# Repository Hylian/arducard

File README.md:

arducard
========

An open-source Arduino derivative e-paper dev device.

Features
-----

* ATmega32U4 (Same as the Arduino Leonardo)
* USB transceiver
* DS1343 Real-Time Clock
* 128KB FRAM
* LiR2016 Coin-cell Li-Ion battery
* Battery charging over USB
* 2.7" e-Paper display
* 5 edge-mounted interrupt-triggered tactile buttons

Dimensions
----------

80 mm x 45 mm x 5 mm

Applications
------------

* Google Auth Time-OTP 
* Store barcodes for rewards cards, etc.
* Store QR codes
* USB text terminal for Raspberry Pi
* ...

Interested?
-----------

Tweet me at [@inwardshed](https://twitter.com/inwardshed) or e-mail at [edshin95@gmail.com](mailto:edshin95@gmail.com) if you're interested in assembling a PCB/contributing.

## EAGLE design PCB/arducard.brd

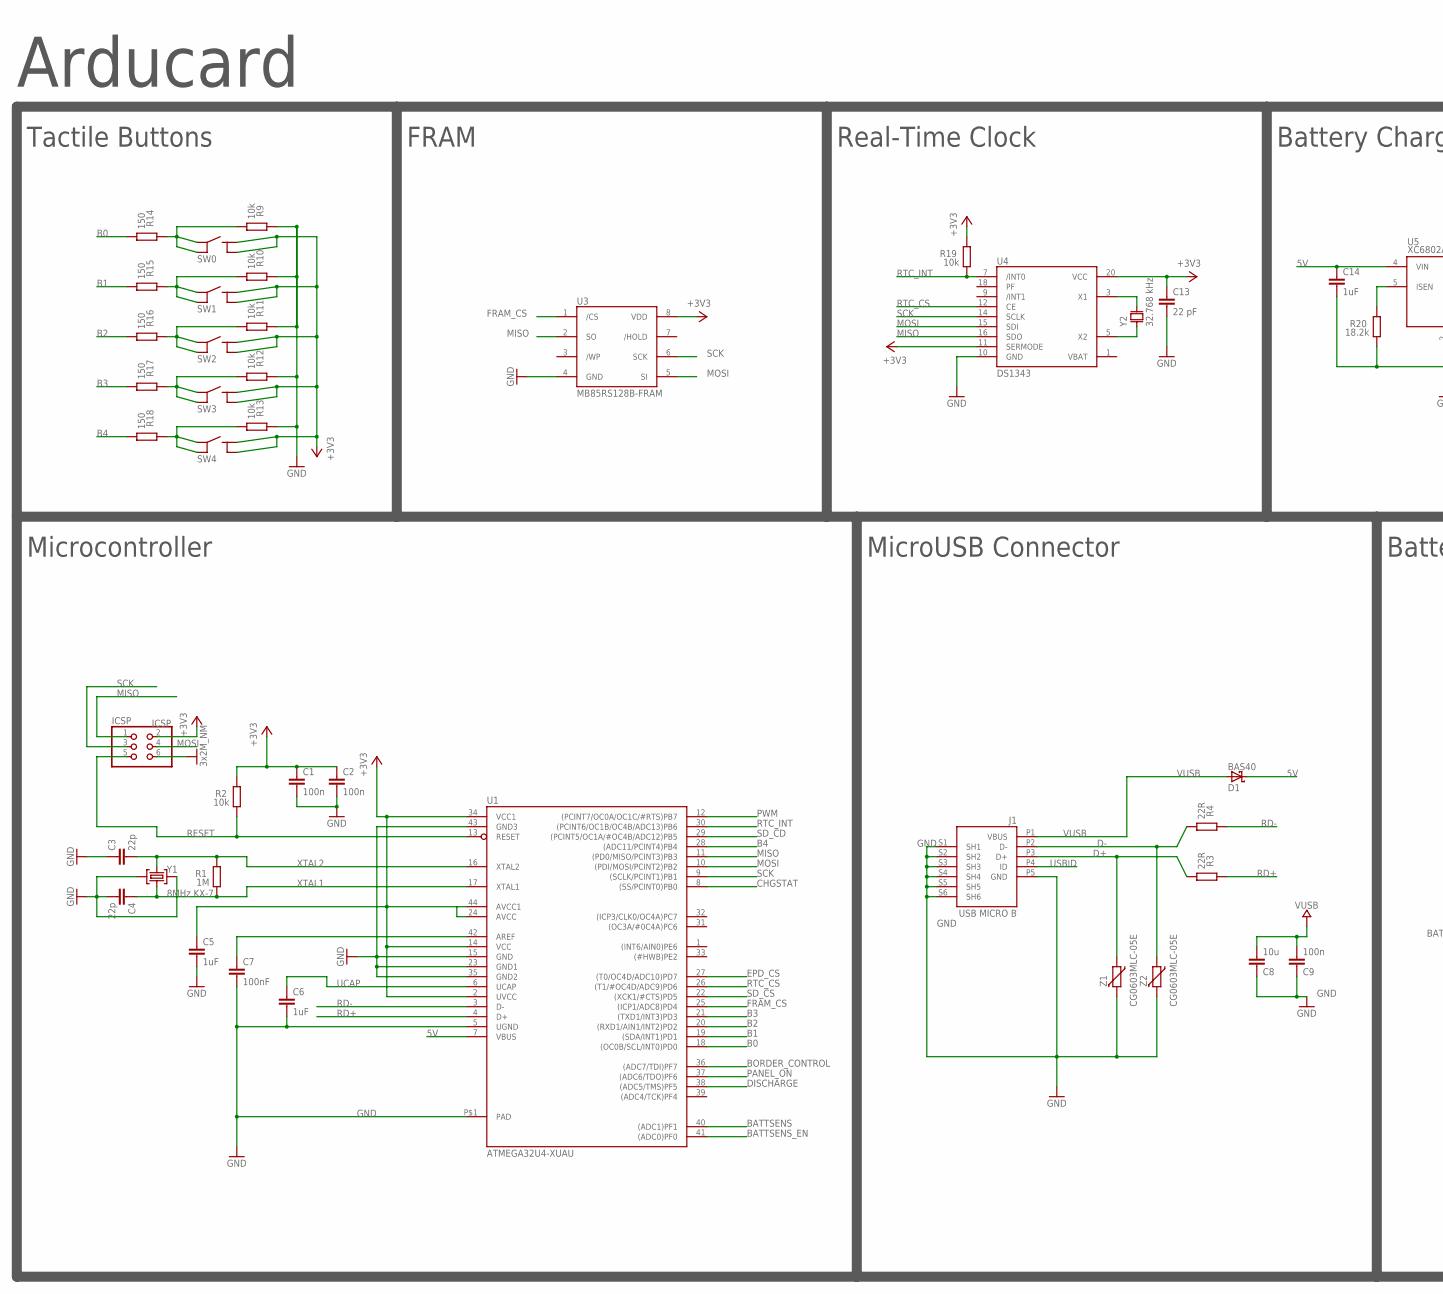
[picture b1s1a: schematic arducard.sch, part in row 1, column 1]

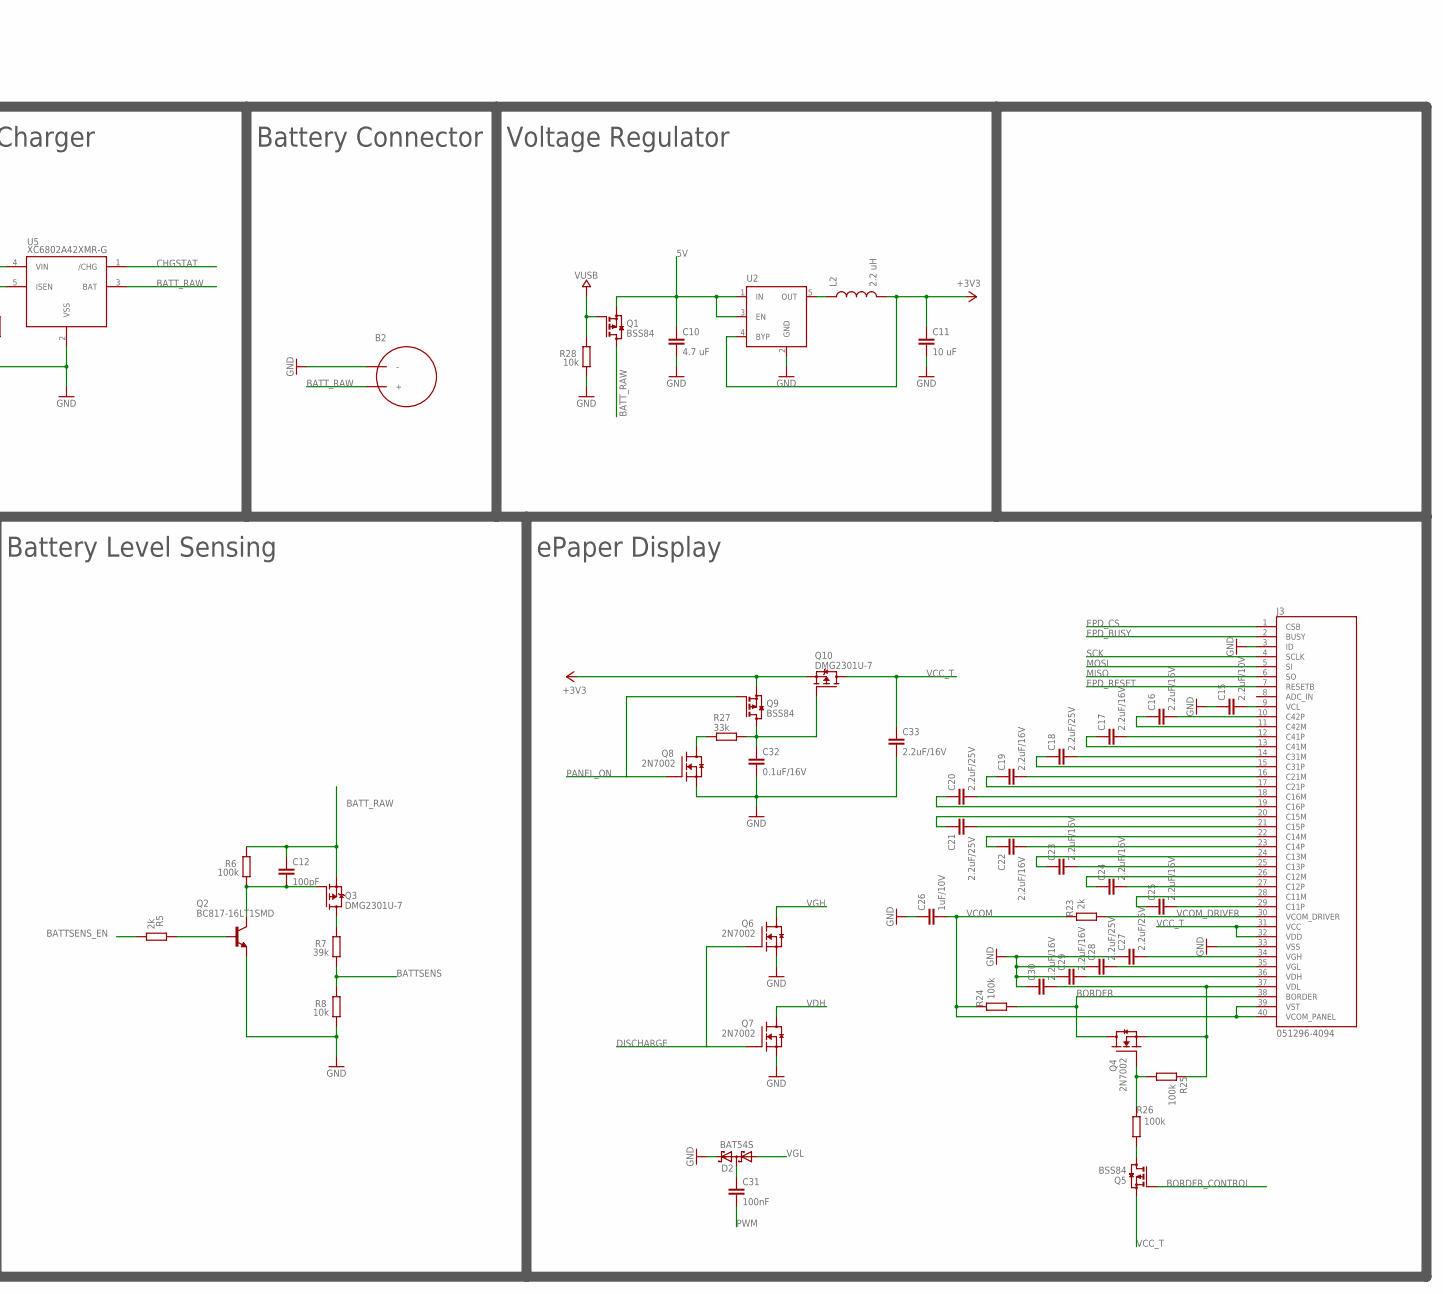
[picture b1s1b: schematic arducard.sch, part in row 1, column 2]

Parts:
B2: LIR2016; BK-5067
C1, C2, C9: 100n; C0603-ROUND
C3, C4: 22p; C0603-ROUND
C5, C6, C14: 1uF; C0603-ROUND
C7, C31: 100nF; C0603-ROUND
C8: 10u; C0603-ROUND
C10: 4.7 uF; C0603-ROUND
C11: 10 uF; C0603-ROUND
C12: 100pF; C0603-ROUND
C13: 22 pF; C0603-ROUND
C15: 2.2uF/10V; C0603-ROUND
C16, C17, C19, C22, C23, C24, C25, C29, C30, C33: 2.2uF/16V; C0603-ROUND
C18, C20, C21, C27, C28: 2.2uF/25V; C0603-ROUND
C26: 1uF/10V; C0603-ROUND
C32: 0.1uF/16V; C0603-ROUND
D1: BAS40; SOT23
D2: BAT54S; SOT23
ICSP: ICSP; 2X03
J1: USB MICRO B; CON2_USB_MICRO_B_AT
J3: 051296-4094
L2: 2.2 uH; 0603
Q1, Q5, Q9: BSS84; SOT23
Q2: BC817-16LT1SMD; SOT23-BEC
Q3, Q10: DMG2301U-7; SOT23
Q4, Q6, Q7, Q8: 2N7002; SOT-23
R1: 1M; R0603-ROUND
R2, R8, R9, R10, R11, R12, R13, R19, R28: 10k; R0603-ROUND
R3, R4: 22R; R0603-ROUND
R5, R23: 2k; R0603-ROUND
R6, R24, R25, R26: 100k; R0603-ROUND
R7: 39k; R0603-ROUND
R14, R15, R16, R17, R18: 150; R0603-ROUND
R20: 18.2k; R0603-ROUND
R27: 33k; R0603-ROUND
SW0, SW1, SW2, SW3, SW4: EVQ-PUA; SMD-TACT-SWITCH
U1: ATMEGA32U4-XUAU; TQFP44-PAD
U2: MIC5219XX; SOT23-5
U3: MB85RS128B-FRAM; SO-08
U4: DS1343; TSSOP20
U5: XC6802A42XMR-G; SOT23-5L
Y1: 8MHz KX-7; CRYSTAL-3.2-2.5
Y2: 32.768 kHz; SSP-T7-F
Z1, Z2: CG0603MLC-05E; CT/CN0603

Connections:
5V: C10.1, C14.1, D1.3 (C), Q1.2 (S), U1.7 (VBUS), U2.1 (IN), U2.3 (EN), U5.4 (VIN)
+3V3: C1.1, C2.1, C5.1, C11.1, C13.1, ICSP.2, L2.2, Q9.2 (S), Q10.2 (S), R2.2, R19.2, SW0.2, SW0.4, SW1.2, SW1.4, SW2.2, SW2.4, SW3.2, SW3.4, SW4.2, SW4.4, U1.2 (UVCC), U1.14 (VCC), U1.24 (AVCC), U1.34 (VCC1), U1.44 (AVCC1), U2.4 (BYP), U3.8 (VDD), U4.11 (SERMODE), U4.20 (VCC)
B0: R14.1, U1.18 ((OC0B/SCL/INT0)PD0)
B1: R15.1, U1.19 ((SDA/INT1)PD1)
B2: R16.1, U1.20 ((RXD1/AIN1/INT2)PD2)
B3: R17.1, U1.21 ((TXD1/INT3)PD3)
B4: R18.1, U1.28 ((ADC11/PCINT4)PB4)
BATTSENS: R7.1, R8.2, U1.40 ((ADC1)PF1)
BATTSENS_EN: R5.1, U1.41 ((ADC0)PF0)
BATT_RAW: B2.POS1 (+), B2.POS2 (+), C12.1, Q1.3 (D), Q3.2 (S), R6.2, U5.3 (BAT)
BORDER: J3.38 (BORDER), Q4.3 (D), R24.2
BORDER_CONTROL: Q5.1 (G), U1.36 ((ADC7/TDI)PF7)
CHGSTAT: U1.8 ((SS/PCINT0)PB0), U5.1 (/CHG)
D+: J1.P3 (D+), R3.1, Z1.1
D-: J1.P2 (D-), R4.1, Z2.1
DISCHARGE: Q6.1 (G), Q7.1 (G), U1.38 ((ADC5/TMS)PF5)
EPD_BUSY: J3.2 (BUSY)
EPD_CS: J3.1 (CSB), U1.27 ((T0/OC4D/ADC10)PD7)
EPD_RESET: J3.7 (RESETB)
FRAM_CS: U1.25 ((ICP1/ADC8)PD4), U3.1 (/CS)
GND: B2.NEG (–), C1.2, C2.2, C3.1, C4.2, C5.2, C6.2, C7.2, C8.1, C9.1, C10.2, C11.2, C13.2, C14.2, C15.1, C26.1, C27.1, C28.1, C29.1, C30.1, C32.2, C33.2, D2.2 (C2), ICSP.6, J1.P5 (GND), J1.S1 (SH1), J1.S2 (SH2), J1.S3 (SH3), J1.S4 (SH4), J1.S5 (SH5), J1.S6 (SH6), J3.3 (ID), J3.33 (VSS), Q2.E, Q6.2 (S), Q7.2 (S), Q8.2 (S), R8.1, R9.2, R10.2, R11.2, R12.2, R13.2, R20.1, R28.1, U1.5 (UGND), U1.15 (GND), U1.23 (GND1), U1.35 (GND2), U1.43 (GND3), U1.P$1 (PAD), U2.2 (GND), U3.4 (GND), U4.10 (GND), U5.2 (VSS), Y1.2 (GND), Y1.4 (GND), Z1.2, Z2.2
MISO: ICSP.1, J3.6 (SO), U1.11 ((PD0/MISO/PCINT3)PB3), U3.2 (SO), U4.16 (SDO)
MOSI: ICSP.4, J3.5 (SI), U1.10 ((PDI/MOSI/PCINT2)PB2), U3.5 (SI), U4.15 (SDI)
unnamed: C15.2, J3.9 (VCL)
unnamed: R10.1, R15.2, SW1.1, SW1.3
unnamed: R9.1, R14.2, SW0.1, SW0.3
unnamed: U4.3 (X1), Y2.P$4
unnamed: R11.1, R16.2, SW2.1, SW2.3
unnamed: R12.1, R17.2, SW3.1, SW3.3
unnamed: L2.1, U2.5 (OUT)
unnamed: R13.1, R18.2, SW4.1, SW4.3
unnamed: C7.1, U1.42 (AREF)
unnamed: C12.2, Q2.C, Q3.1 (G), R6.1
unnamed: C16.2, J3.10 (C42P)
unnamed: Q3.3 (D), R7.2
unnamed: C16.1, J3.11 (C42M)
unnamed: C17.2, J3.12 (C41P)
unnamed: C17.1, J3.13 (C41M)
unnamed: U4.5 (X2), Y2.P$1
unnamed: C18.2, J3.14 (C31M)
unnamed: C18.1, J3.15 (C31P)
unnamed: C19.2, J3.16 (C21M)
unnamed: C19.1, J3.17 (C21P)
unnamed: C20.2, J3.18 (C16M)
unnamed: C20.1, J3.19 (C16P)
unnamed: C21.1, J3.20 (C15M)
unnamed: C21.2, J3.21 (C15P)
unnamed: C22.2, J3.23 (C14P)
unnamed: C22.1, J3.22 (C14M)
unnamed: C23.2, J3.25 (C13P)
unnamed: C23.1, J3.24 (C13M)
unnamed: C24.2, J3.27 (C12P)
unnamed: C24.1, J3.26 (C12M)
unnamed: C25.2, J3.29 (C11P)
unnamed: C25.1, J3.28 (C11M)
unnamed: Q8.3 (D), R27.1
unnamed: R20.2, U5.5 (ISEN)
unnamed: Q5.3 (D), R26.2
unnamed: Q4.1 (G), R25.2, R26.1
unnamed: C31.1, D2.3 (C1A2)
unnamed: C32.1, Q9.3 (D), Q10.1 (G), R27.2
PANEL_ON: Q8.1 (G), Q9.1 (G), U1.37 ((ADC6/TDO)PF6)
PWM: C31.2, U1.12 ((PCINT7/OC0A/OC1C/#RTS)PB7)
Q2: Q2.B, R5.2
RD+: R3.2, U1.4 (D+)
RD-: R4.2, U1.3 (D-)
RESET: ICSP.5, R2.1, U1.13 (RESET)
RTC_CS: U1.26 ((T1/#OC4D/ADC9)PD6), U4.12 (CE)
RTC_INT: R19.1, U1.30 ((PCINT6/OC1B/OC4B/ADC13)PB6), U4.7 (/INT0)
SCK: ICSP.3, J3.4 (SCLK), U1.9 ((SCLK/PCINT1)PB1), U3.6 (SCK), U4.14 (SCLK)
SD_CD: U1.29 ((PCINT5/OC1A/#OC4B/ADC12)PB5)
SD_CS: U1.22 ((XCK1/#CTS)PD5)
UCAP: C6.1, U1.6 (UCAP)
USBID: J1.P4 (ID)
VCC_T: C33.1, J3.31 (VCC), J3.32 (VDD), Q5.2 (S), Q10.3 (D)
VCOM: C26.2, J3.39 (VST), J3.40 (VCOM_PANEL), R23.1, R24.1
VCOM_DRIVER: J3.30 (VCOM_DRIVER), R23.2
VDH: C29.2, J3.36 (VDH), Q7.3 (D)
VDL: C30.2, J3.37 (VDL), Q4.2 (S), R25.1
VGH: C27.2, J3.34 (VGH), Q6.3 (D)
VGL: C28.2, D2.1 (A1), J3.35 (VGL)
VUSB: C8.2, C9.2, D1.1 (A), J1.P1 (VBUS), Q1.1 (G), R28.2
XTAL1: C4.1, R1.1, U1.17 (XTAL1), Y1.1 (C1)
XTAL2: C3.2, R1.2, U1.16 (XTAL2), Y1.3 (C2)

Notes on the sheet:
Voltage Regulator
Battery Connector
Battery Charger
Real-Time Clock
FRAM
Tactile Buttons
Microcontroller
MicroUSB Connector
Battery Level Sensing
ePaper Display
Arducard

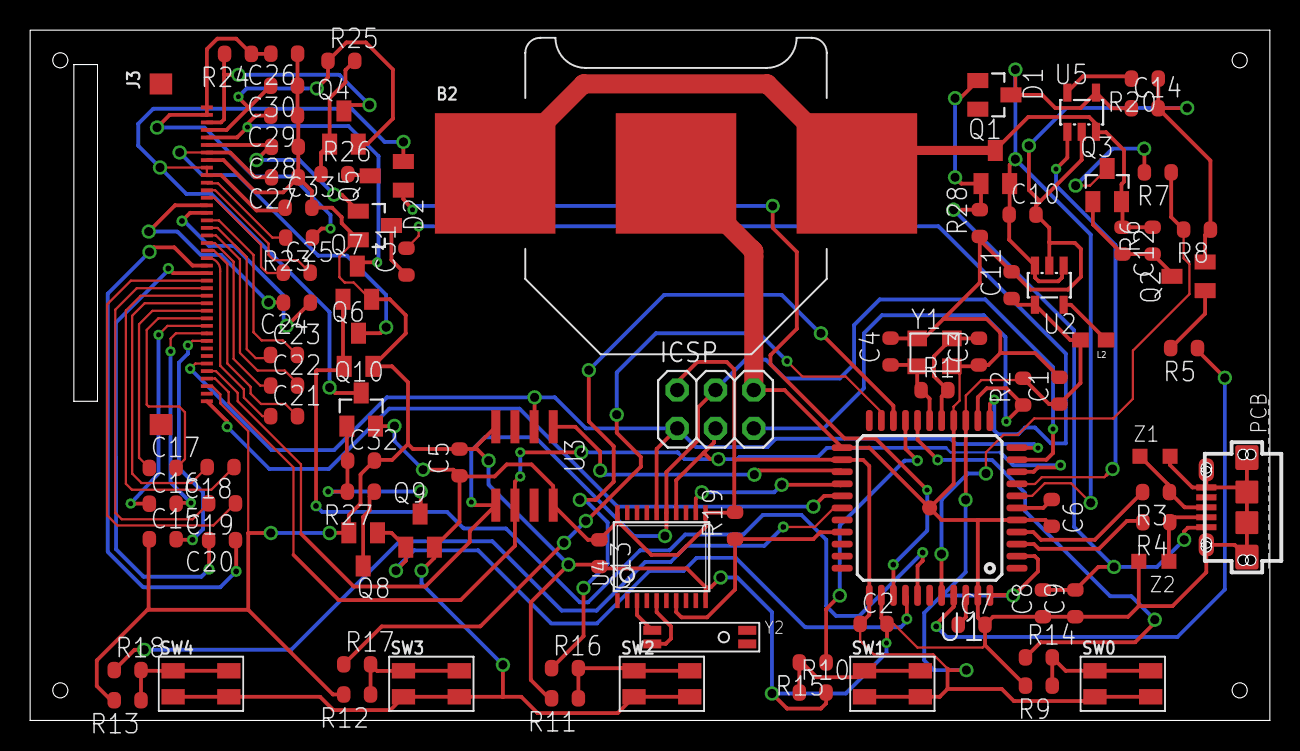
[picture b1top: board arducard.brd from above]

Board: 2 copper layers, 82.3 x 45.8 mm, 90 parts (0 on the bottom side), 79 nets.

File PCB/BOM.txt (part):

Partlist

Exported from arducard.sch at 4/12/2014 8:20:19 PM

EAGLE Version 6.5.0 Copyright (c) 1988-2013 CadSoft

Assembly variant: 

Part     Value           Device             Package             Library                 Sheet

B2       LIR2016         LIR2016            BK-5067             arducard-coincell       1
C1       100n            C-EUC0603          C0603-ROUND         SmartPrj                1
C2       100n            C-EUC0603          C0603-ROUND         SmartPrj                1
C3       22p             C-EUC0603          C0603-ROUND         SmartPrj                1
C4       22p             C-EUC0603          C0603-ROUND         SmartPrj                1
C5       1uF             C-EUC0603          C0603-ROUND         SmartPrj                1
C6       1uF             C-EUC0603          C0603-ROUND         SmartPrj                1
C7       100nF           C-EUC0603          C0603-ROUND         SmartPrj                1
C8       10u             C-EUC0603          C0603-ROUND         SmartPrj                1
C9       100n            C-EUC0603          C0603-ROUND         SmartPrj                1
C10      4.7 uF          C-EUC0603          C0603-ROUND         SmartPrj                1
C11      10 uF           C-EUC0603          C0603-ROUND         SmartPrj                1
C12      100pF           C-EUC0603          C0603-ROUND         SmartPrj                1
C13      22 pF           C-EUC0603          C0603-ROUND         SmartPrj                1
C14      1uF             C-EUC0603          C0603-ROUND         SmartPrj                1
C15      2.2uF/10V       C-EUC0603          C0603-ROUND         SmartPrj                1
C16      2.2uF/16V       C-EUC0603          C0603-ROUND         SmartPrj                1
C17      2.2uF/16V       C-EUC0603          C0603-ROUND         SmartPrj                1
C18      2.2uF/25V       C-EUC0603          C0603-ROUND         SmartPrj                1
C19      2.2uF/16V       C-EUC0603          C0603-ROUND         SmartPrj                1
C20      2.2uF/25V       C-EUC0603          C0603-ROUND         SmartPrj                1
C21      2.2uF/25V       C-EUC0603          C0603-ROUND         SmartPrj                1
C22      2.2uF/16V       C-EUC0603          C0603-ROUND         SmartPrj                1
C23      2.2uF/16V       C-EUC0603          C0603-ROUND         SmartPrj                1
C24      2.2uF/16V       C-EUC0603          C0603-ROUND         SmartPrj                1
C25      2.2uF/16V       C-EUC0603          C0603-ROUND         SmartPrj                1
C26      1uF/10V         C-EUC0603          C0603-ROUND         SmartPrj                1
C27      2.2uF/25V       C-EUC0603          C0603-ROUND         SmartPrj                1
C28      2.2uF/25V       C-EUC0603          C0603-ROUND         SmartPrj                1
C29      2.2uF/16V       C-EUC0603          C0603-ROUND         SmartPrj                1
C30      2.2uF/16V       C-EUC0603          C0603-ROUND         SmartPrj                1
C31      100nF           C-EUC0603          C0603-ROUND         SmartPrj                1
C32      0.1uF/16V       C-EUC0603          C0603-ROUND         SmartPrj                1
C33      2.2uF/16V       C-EUC0603          C0603-ROUND         SmartPrj                1
D1       BAS40           BAS40              SOT23               diode                   1
D2       BAT54S          BAT54S             SOT23               diode                   1
ICSP     ICSP            PINHD-2X3          2X03                SmartPrj                1
J1       USB MICRO B     MYCON2_USB-MINI-B  CON2_USB_MICRO_B_AT SmartPrj                1
J3       051296-4094     051296-4094        051296-4094         arducard-fpc            1
L2       2.2 uH          INDUCTOR30OHM,1.8A 0603                SparkFun-Passives       1
Q1       BSS84           BSS84              SOT23               transistor-small-signal 1
Q2       BC817-16LT1SMD  BC817-16LT1SMD     SOT23-BEC           transistor-npn          1
Q3       DMG2301U-7      DMG2301U-7         SOT23               transistor-fet          1
Q4       2N7002          2N7002             SOT-23              AWJLEagleLib            1
Q5       BSS84           BSS84              SOT23               transistor-small-signal 1
Q6       2N7002          2N7002             SOT-23              AWJLEagleLib            1
Q7       2N7002          2N7002             SOT-23              AWJLEagleLib            1
Q8       2N7002          2N7002             SOT-23              AWJLEagleLib            1
Q9       BSS84           BSS84              SOT23               transistor-small-signal 1
Q10      DMG2301U-7      DMG2301U-7         SOT23               transistor-fet          1
R1       1M              R-EU_R0603         R0603-ROUND         SmartPrj                1
R2       10k             R-EU_R0603         R0603-ROUND         SmartPrj                1
R3       22R             R-EU_R0603         R0603-ROUND         SmartPrj                1
R4       22R             R-EU_R0603         R0603-ROUND         SmartPrj                1
R5       2k              R-EU_R0603         R0603-ROUND         SmartPrj                1
R6       100k            R-EU_R0603         R0603-ROUND         SmartPrj                1
R7       39k             R-EU_R0603         R0603-ROUND         SmartPrj                1
R8       10k             R-EU_R0603         R0603-ROUND         SmartPrj                1
R9       10k             R-EU_R0603         R0603-ROUND         SmartPrj                1
R10      10k             R-EU_R0603         R0603-ROUND         SmartPrj                1
R11      10k             R-EU_R0603         R0603-ROUND         SmartPrj                1
R12      10k             R-EU_R0603         R0603-ROUND         SmartPrj                1
R13      10k             R-EU_R0603         R0603-ROUND         SmartPrj                1
R14      150             R-EU_R0603         R0603-ROUND         SmartPrj                1
R15      150             R-EU_R0603         R0603-ROUND         SmartPrj                1
R16      150             R-EU_R0603         R0603-ROUND         SmartPrj                1
R17      150             R-EU_R0603         R0603-ROUND         SmartPrj                1
R18      150             R-EU_R0603         R0603-ROUND         SmartPrj                1
R19      10k             R-EU_R0603         R0603-ROUND         SmartPrj                1
R20      18.2k           R-EU_R0603         R0603-ROUND         SmartPrj                1
R23      2k              R-EU_R0603         R0603-ROUND         SmartPrj                1
R24      100k            R-EU_R0603         R0603-ROUND         SmartPrj                1
R25      100k            R-EU_R0603         R0603-ROUND         SmartPrj                1
R26      100k            R-EU_R0603         R0603-ROUND         SmartPrj                1
R27      33k             R-EU_R0603         R0603-ROUND         SmartPrj                1
R28      10k             R-EU_R0603         R0603-ROUND         SmartPrj                1
SW0      EVQ-PUA         EVQ-PUA            SMD-TACT-SWITCH     arducard-switch         1
SW1      EVQ-PUA         EVQ-PUA            SMD-TACT-SWITCH     arducard-switch         1
SW2      EVQ-PUA         EVQ-PUA            SMD-TACT-SWITCH     arducard-switch         1
SW3      EVQ-PUA         EVQ-PUA            SMD-TACT-SWITCH     arducard-switch         1
SW4      EVQ-PUA         EVQ-PUA            SMD-TACT-SWITCH     arducard-switch         1
U1       ATMEGA32U4-XUAU ATMEGA32U4-XUAU    TQFP44-PAD          SmartPrj                1
U2                       MIC5219XX          SOT23-5             v-reg-micrel            1
U3       MB85RS128B-FRAM MB85RS128B-FRAM    SO-08               arducard-fram           1
U4       DS1343          DS1343             TSSOP20             arducard-rtc            1
U5       XC6802A42XMR-G  XC6802A42XMR-G     SOT23-5L            arducard-xc6802         1
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
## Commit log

2014-01-02 Very preliminary PCB design; everything except display circuit
2014-02-23 Added DS3234 Real Time Clock
2014-02-24 Added display ZIF connector and control circuit
2014-02-24 Added voltage ratings to display control circuit
2014-02-25 Added EPD panel on control
2014-02-25 Changed battery level sensing transistor
2014-03-02 Added extra button
2014-03-09 added battery connector
2014-03-10 changed SRAM to FRAM
2014-03-10 added 5th button
2014-03-10 removed reset switch
2014-03-11 added coin cell battery
2014-03-12 changed RTC to DS1343
2014-03-12 added bypass cap to vreg input
2014-03-12 organized schematic layout
2014-03-13 added switch between Vusb and battery
2014-03-13 fixed up libraries
2014-03-14 initial board layout
2014-03-14 removed microsd
2014-03-29 fixed VUSB diode
2014-03-29 removed flat cell battery connector
2014-04-12 initial routing for dorkbot
2014-04-13 added gerber for stencil and fixed missing trace
2014-04-15 added README content
2014-04-15 added button description
2014-04-15 added potential applications
2014-04-15 added interested section
2014-04-26 renamed a part
2014-04-26 FRAM ID check test code

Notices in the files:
parts and their libraries:
SparkFun-Passives: Licensing: CC v3.0 Share-Alike You are welcome to use this library for commercial purposes.
